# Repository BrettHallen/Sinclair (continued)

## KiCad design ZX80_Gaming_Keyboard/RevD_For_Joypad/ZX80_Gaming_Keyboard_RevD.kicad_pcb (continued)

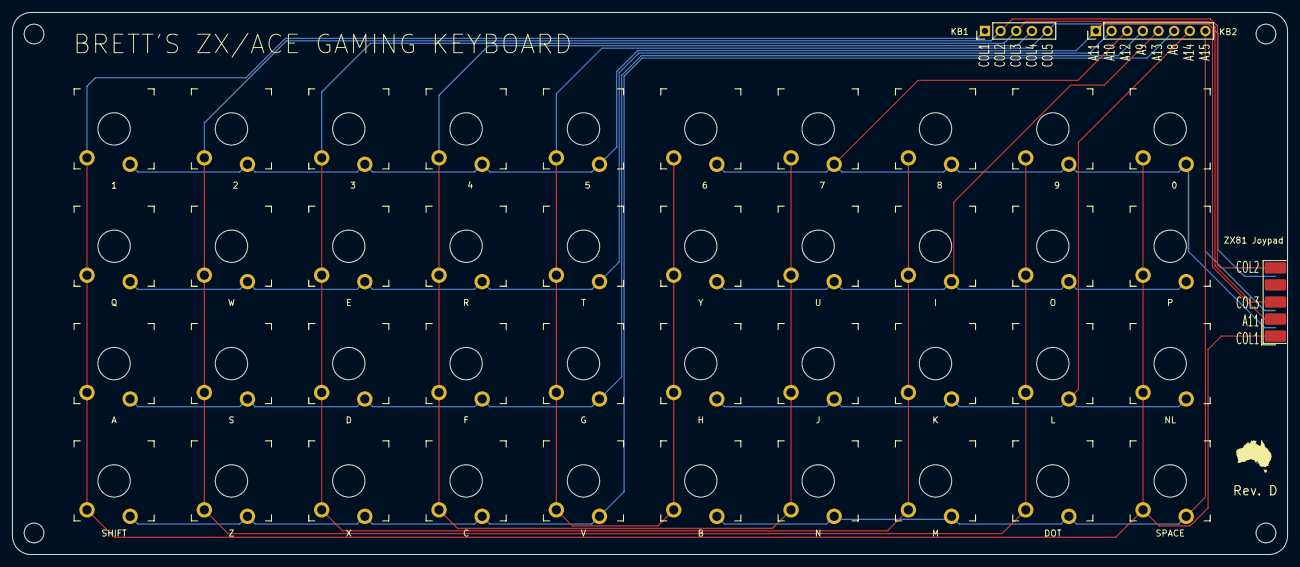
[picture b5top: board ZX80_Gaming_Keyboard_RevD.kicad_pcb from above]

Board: 2 copper layers, 207.0 x 88.0 mm, 47 parts (0 on the bottom side), 13 nets.

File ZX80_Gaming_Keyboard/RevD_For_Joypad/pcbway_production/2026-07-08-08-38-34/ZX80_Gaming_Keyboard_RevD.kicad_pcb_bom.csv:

Designator,Quantity,Value,Footprint,Package,MPN,DNP,Mount_Type,Description,KiLib_Generator
J1,1,KB1,PinHeader_1x05_P2.54mm_Vertical,,,,tht,"Generic connector, single row, 01x05, script generated (kicad-library-utils/schlib/autogen/connector/)",
J2,1,ZX81 Joypad,DSUB-9_Pins_EdgeMount_P2.77mm,,,,smt,"9-pin D-SUB connector, pins (male)",connector/D_sub
J3,1,KB2,PinHeader_1x08_P2.54mm_Vertical,,,,tht,"Generic connector, single row, 01x08, script generated (kicad-library-utils/schlib/autogen/connector/)",
SW1,1,1,SW_Gateron_LowProfile_THT,,,,tht,"Push button switch, normally open, two pins, 45° tilted",
SW10,1,E,SW_Gateron_LowProfile_THT,,,,tht,"Push button switch, normally open, two pins, 45° tilted",
SW11,1,D,SW_Gateron_LowProfile_THT,,,,tht,"Push button switch, normally open, two pins, 45° tilted",
SW12,1,X,SW_Gateron_LowProfile_THT,,,,tht,"Push button switch, normally open, two pins, 45° tilted",
SW13,1,4,SW_Gateron_LowProfile_THT,,,,tht,"Push button switch, normally open, two pins, 45° tilted",
SW14,1,R,SW_Gateron_LowProfile_THT,,,,tht,"Push button switch, normally open, two pins, 45° tilted",
SW15,1,F,SW_Gateron_LowProfile_THT,,,,tht,"Push button switch, normally open, two pins, 45° tilted",
SW16,1,C,SW_Gateron_LowProfile_THT,,,,tht,"Push button switch, normally open, two pins, 45° tilted",
SW17,1,5,SW_Gateron_LowProfile_THT,,,,tht,"Push button switch, normally open, two pins, 45° tilted",
SW18,1,T,SW_Gateron_LowProfile_THT,,,,tht,"Push button switch, normally open, two pins, 45° tilted",
SW19,1,G,SW_Gateron_LowProfile_THT,,,,tht,"Push button switch, normally open, two pins, 45° tilted",
SW2,1,Q,SW_Gateron_LowProfile_THT,,,,tht,"Push button switch, normally open, two pins, 45° tilted",
SW20,1,V,SW_Gateron_LowProfile_THT,,,,tht,"Push button switch, normally open, two pins, 45° tilted",
SW21,1,6,SW_Gateron_LowProfile_THT,,,,tht,"Push button switch, normally open, two pins, 45° tilted",
SW22,1,Y,SW_Gateron_LowProfile_THT,,,,tht,"Push button switch, normally open, two pins, 45° tilted",
SW23,1,H,SW_Gateron_LowProfile_THT,,,,tht,"Push button switch, normally open, two pins, 45° tilted",
SW24,1,B,SW_Gateron_LowProfile_THT,,,,tht,"Push button switch, normally open, two pins, 45° tilted",
SW25,1,7,SW_Gateron_LowProfile_THT,,,,tht,"Push button switch, normally open, two pins, 45° tilted",
SW26,1,U,SW_Gateron_LowProfile_THT,,,,tht,"Push button switch, normally open, two pins, 45° tilted",
SW27,1,J,SW_Gateron_LowProfile_THT,,,,tht,"Push button switch, normally open, two pins, 45° tilted",
SW28,1,N,SW_Gateron_LowProfile_THT,,,,tht,"Push button switch, normally open, two pins, 45° tilted",
SW29,1,8,SW_Gateron_LowProfile_THT,,,,tht,"Push button switch, normally open, two pins, 45° tilted",
SW3,1,A,SW_Gateron_LowProfile_THT,,,,tht,"Push button switch, normally open, two pins, 45° tilted",
SW30,1,I,SW_Gateron_LowProfile_THT,,,,tht,"Push button switch, normally open, two pins, 45° tilted",
SW31,1,K,SW_Gateron_LowProfile_THT,,,,tht,"Push button switch, normally open, two pins, 45° tilted",
SW32,1,M,SW_Gateron_LowProfile_THT,,,,tht,"Push button switch, normally open, two pins, 45° tilted",
SW33,1,9,SW_Gateron_LowProfile_THT,,,,tht,"Push button switch, normally open, two pins, 45° tilted",
SW34,1,O,SW_Gateron_LowProfile_THT,,,,tht,"Push button switch, normally open, two pins, 45° tilted",
SW35,1,L,SW_Gateron_LowProfile_THT,,,,tht,"Push button switch, normally open, two pins, 45° tilted",
SW36,1,DOT,SW_Gateron_LowProfile_THT,,,,tht,"Push button switch, normally open, two pins, 45° tilted",
SW37,1,0,SW_Gateron_LowProfile_THT,,,,tht,"Push button switch, normally open, two pins, 45° tilted",
SW38,1,P,SW_Gateron_LowProfile_THT,,,,tht,"Push button switch, normally open, two pins, 45° tilted",
SW39,1,NL,SW_Gateron_LowProfile_THT,,,,tht,"Push button switch, normally open, two pins, 45° tilted",
SW4,1,SHIFT,SW_Gateron_LowProfile_THT,,,,tht,"Push button switch, normally open, two pins, 45° tilted",
SW40,1,SPACE,SW_Gateron_LowProfile_THT,,,,tht,"Push button switch, normally open, two pins, 45° tilted",
SW5,1,2,SW_Gateron_LowProfile_THT,,,,tht,"Push button switch, normally open, two pins, 45° tilted",
SW6,1,W,SW_Gateron_LowProfile_THT,,,,tht,"Push button switch, normally open, two pins, 45° tilted",
SW7,1,S,SW_Gateron_LowProfile_THT,,,,tht,"Push button switch, normally open, two pins, 45° tilted",
SW8,1,Z,SW_Gateron_LowProfile_THT,,,,tht,"Push button switch, normally open, two pins, 45° tilted",
SW9,1,3,SW_Gateron_LowProfile_THT,,,,tht,"Push button switch, normally open, two pins, 45° tilted",

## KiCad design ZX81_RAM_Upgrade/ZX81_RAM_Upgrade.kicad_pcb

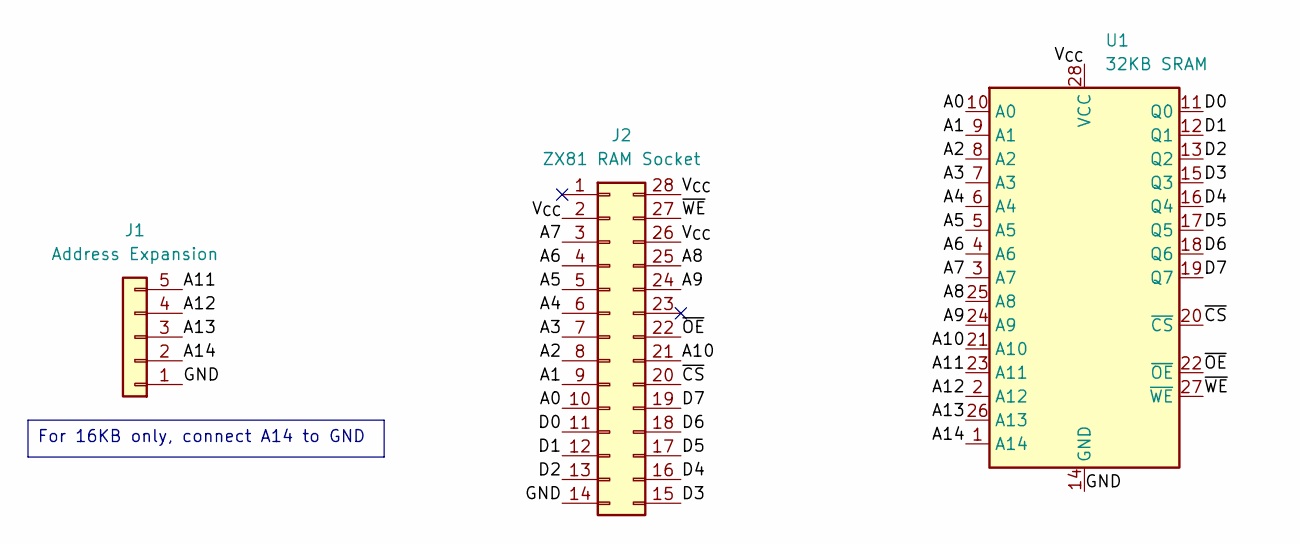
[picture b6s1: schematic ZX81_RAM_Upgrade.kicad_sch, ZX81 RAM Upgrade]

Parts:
J1: Address Expansion; PinHeader_1x05_P2.54mm_Vertical
J2: ZX81 RAM Socket; DIP-28_W15.24mm_Socket
U1: 32KB SRAM; DIP-28_W15.24mm

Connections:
/A0: J2.10, U1.10 (A0)
/A1: J2.9, U1.9 (A1)
/A2: J2.8, U1.8 (A2)
/A3: J2.7, U1.7 (A3)
/A4: J2.6, U1.6 (A4)
/A5: J2.5, U1.5 (A5)
/A6: J2.4, U1.4 (A6)
/A7: J2.3, U1.3 (A7)
/A8: J2.25, U1.25 (A8)
/A9: J2.24, U1.24 (A9)
/A10: J2.21, U1.21 (A10)
/A11: J1.5, U1.23 (A11)
/A12: J1.4, U1.2 (A12)
/A13: J1.3, U1.26 (A13)
/A14: J1.2, U1.1 (A14)
/D0: J2.11, U1.11 (Q0)
/D1: J2.12, U1.12 (Q1)
/D2: J2.13, U1.13 (Q2)
/D3: J2.15, U1.15 (Q3)
/D4: J2.16, U1.16 (Q4)
/D5: J2.17, U1.17 (Q5)
/D6: J2.18, U1.18 (Q6)
/D7: J2.19, U1.19 (Q7)
/GND: J1.1, J2.14, U1.14 (GND)
/V_{CC}: J2.2, J2.26, J2.28, U1.28 (VCC)
/~CS: J2.20, U1.20 (~CS)
/~OE: J2.22, U1.22 (~OE)
/~WE: J2.27, U1.27 (~WE)

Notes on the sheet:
For 16KB only, connect A14 to GND

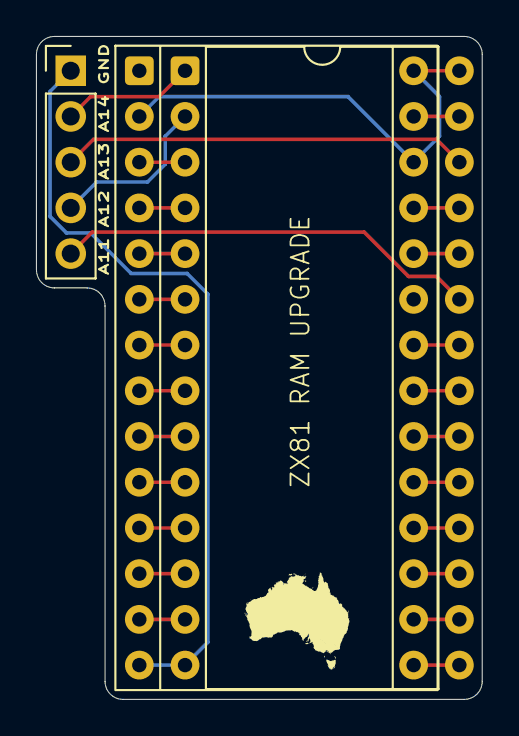
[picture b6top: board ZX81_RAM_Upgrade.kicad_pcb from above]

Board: 2 copper layers, 24.8 x 36.8 mm, 3 parts (0 on the bottom side), 28 nets.

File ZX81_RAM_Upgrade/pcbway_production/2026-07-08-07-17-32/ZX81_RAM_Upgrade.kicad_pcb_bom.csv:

Designator,Quantity,Value,Footprint,Package,MPN,DNP,Mount_Type,Description,KiLib_Generator
J1,1,Address Expansion,PinHeader_1x05_P2.54mm_Vertical,,,,tht,"Generic connector, single row, 01x05, script generated (kicad-library-utils/schlib/autogen/connector/)",connector/pin_header_socket
J2,1,ZX81 RAM Socket,DIP-28_W15.24mm_Socket,,,,tht,"Generic connector, double row, 02x14, counter clockwise pin numbering scheme (similar to DIP package numbering), script generated (kicad-library-utils/schlib/autogen/connector/)",package/DIP/legacy
U1,1,32KB SRAM,DIP-28_W15.24mm,,,,tht,"32Kx8 bit Low Power CMOS Static RAM, 55/70ns, DIP-28",package/DIP/legacy

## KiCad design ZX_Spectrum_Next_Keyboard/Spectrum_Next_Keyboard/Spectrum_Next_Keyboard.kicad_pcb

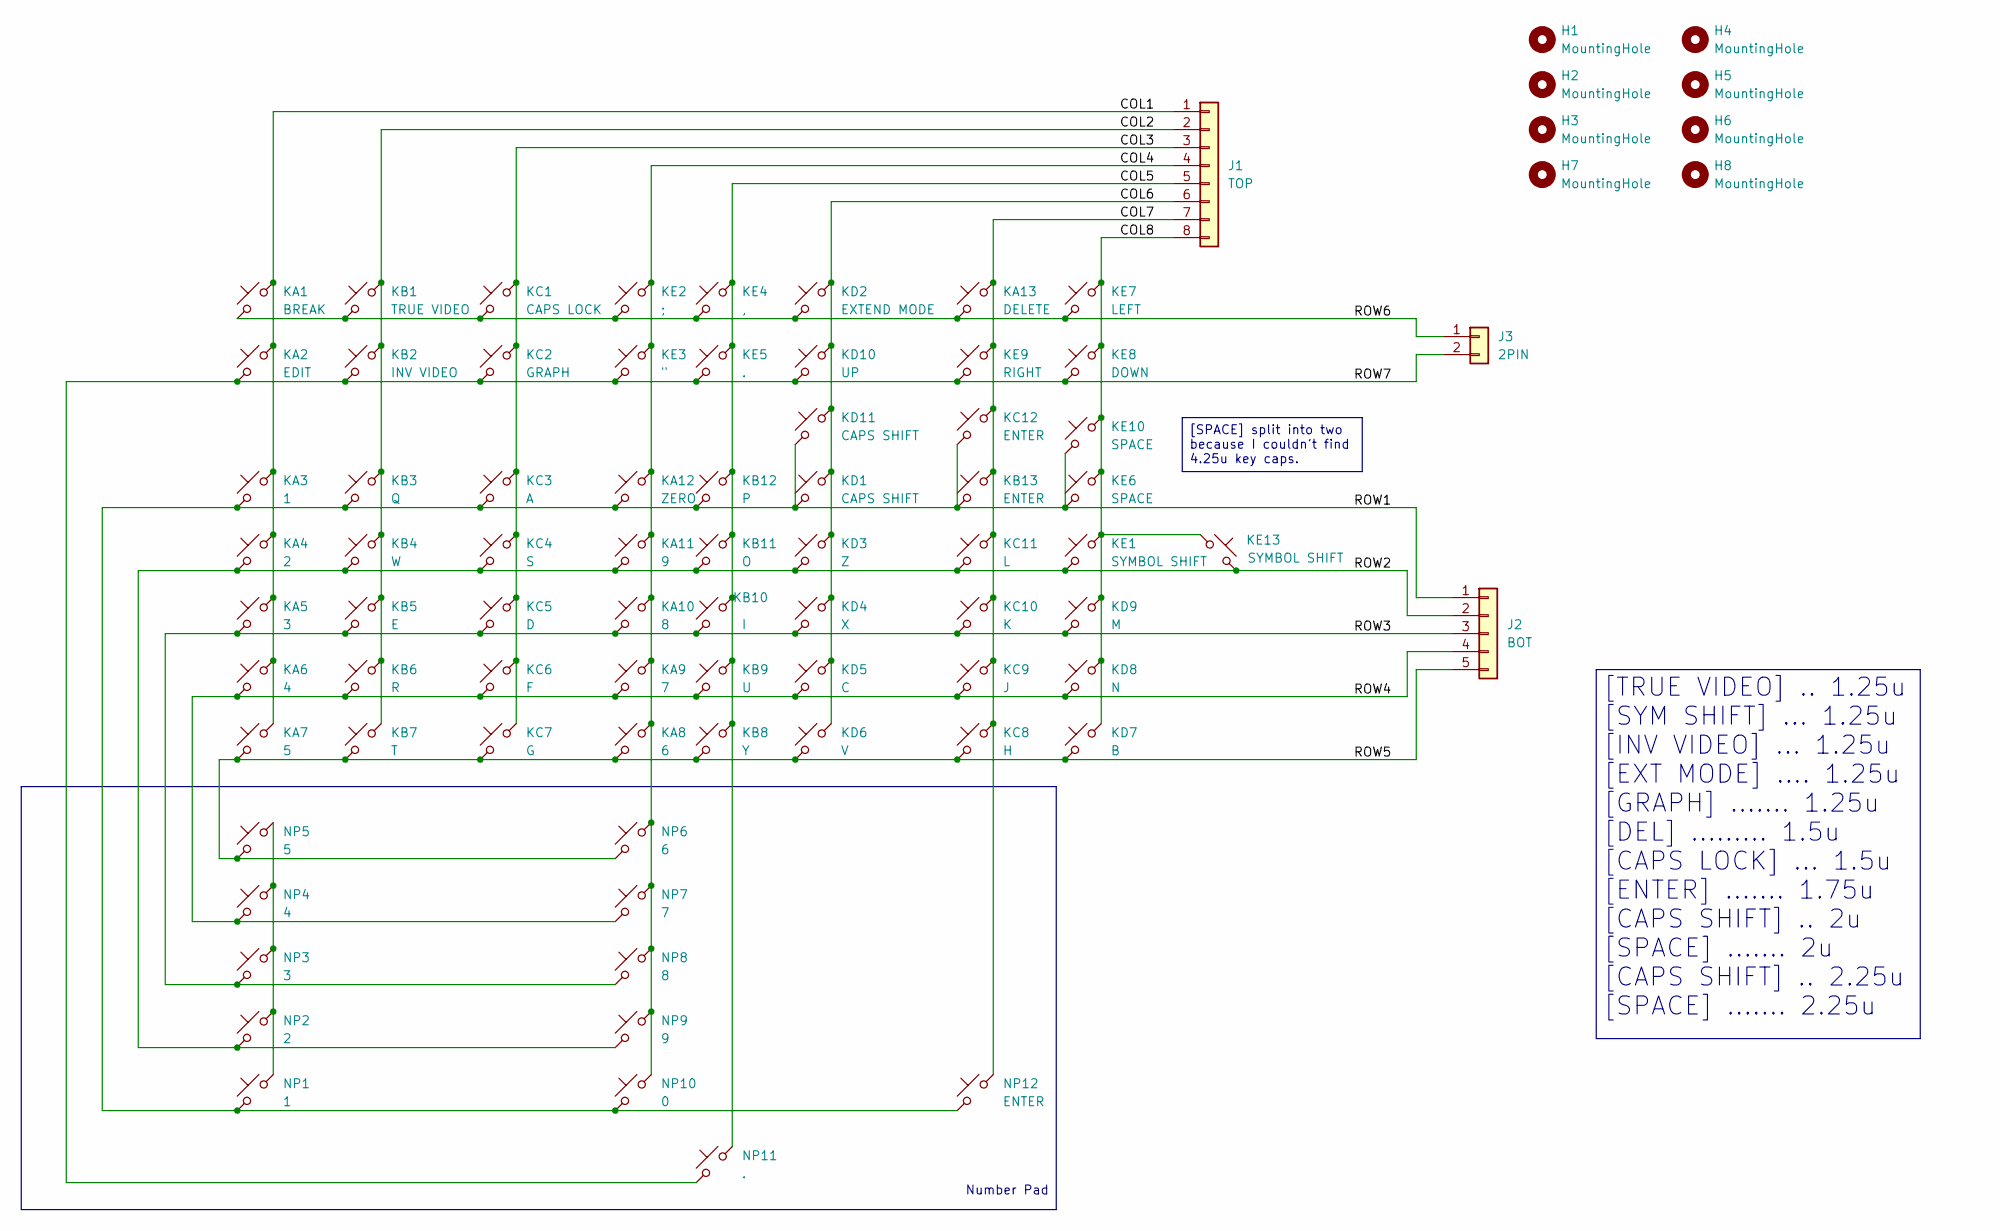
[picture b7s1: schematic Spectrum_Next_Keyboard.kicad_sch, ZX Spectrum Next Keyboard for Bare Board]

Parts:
H1, H2, H3, H4, H5, H6, H7, H8: MountingHole; MountingHole_3.2mm_M3
J1: TOP; PinHeader_1x08_P2.54mm_Vertical
J2: BOT; PinHeader_1x05_P2.54mm_Vertical
J3: 2PIN; PinHeader_1x02_P2.54mm_Vertical
KA1: BREAK; SW_Gateron_LowProfile_THT
KA2: EDIT; SW_Gateron_LowProfile_THT
KA3: 1; SW_Gateron_LowProfile_THT
KA4: 2; SW_Gateron_LowProfile_THT
KA5: 3; SW_Gateron_LowProfile_THT
KA6: 4; SW_Gateron_LowProfile_THT
KA7: 5; SW_Gateron_LowProfile_THT
KA8: 6; SW_Gateron_LowProfile_THT
KA9: 7; SW_Gateron_LowProfile_THT
KA10: 8; SW_Gateron_LowProfile_THT
KA11: 9; SW_Gateron_LowProfile_THT
KA12: ZERO; SW_Gateron_LowProfile_THT
KA13: DELETE; SW_Gateron_LowProfile_THT
KB1: TRUE VIDEO; SW_Gateron_LowProfile_THT
KB2: INV VIDEO; SW_Gateron_LowProfile_THT
KB3: Q; SW_Gateron_LowProfile_THT
KB4: W; SW_Gateron_LowProfile_THT
KB5: E; SW_Gateron_LowProfile_THT
KB6: R; SW_Gateron_LowProfile_THT
KB7: T; SW_Gateron_LowProfile_THT
KB8: Y; SW_Gateron_LowProfile_THT
KB9: U; SW_Gateron_LowProfile_THT
KB10: I; SW_Gateron_LowProfile_THT
KB11: O; SW_Gateron_LowProfile_THT
KB12: P; SW_Gateron_LowProfile_THT
KB13: ENTER; SW_Gateron_LowProfile_THT
KC1: CAPS LOCK; SW_Gateron_LowProfile_THT
KC2: GRAPH; SW_Gateron_LowProfile_THT
KC3: A; SW_Gateron_LowProfile_THT
KC4: S; SW_Gateron_LowProfile_THT
KC5: D; SW_Gateron_LowProfile_THT
KC6: F; SW_Gateron_LowProfile_THT
KC7: G; SW_Gateron_LowProfile_THT
KC8: H; SW_Gateron_LowProfile_THT
KC9: J; SW_Gateron_LowProfile_THT
KC10: K; SW_Gateron_LowProfile_THT
KC11: L; SW_Gateron_LowProfile_THT
KC12: ENTER; SW_Gateron_LowProfile_THT
KD1, KD11: CAPS SHIFT; SW_Gateron_LowProfile_THT
KD2: EXTEND MODE; SW_Gateron_LowProfile_THT
KD3: Z; SW_Gateron_LowProfile_THT
KD4: X; SW_Gateron_LowProfile_THT
KD5: C; SW_Gateron_LowProfile_THT
KD6: V; SW_Gateron_LowProfile_THT
KD7: B; SW_Gateron_LowProfile_THT
KD8: N; SW_Gateron_LowProfile_THT
KD9: M; SW_Gateron_LowProfile_THT
KD10: UP; SW_Gateron_LowProfile_THT
KE1, KE13: SYMBOL SHIFT; SW_Gateron_LowProfile_THT
KE2: ;; SW_Gateron_LowProfile_THT
KE3: "; SW_Gateron_LowProfile_THT
KE4: ,; SW_Gateron_LowProfile_THT
KE5: .; SW_Gateron_LowProfile_THT
KE6, KE10: SPACE; SW_Gateron_LowProfile_THT
KE7: LEFT; SW_Gateron_LowProfile_THT
KE8: DOWN; SW_Gateron_LowProfile_THT
KE9: RIGHT; SW_Gateron_LowProfile_THT
NP1: 1; SW_Gateron_LowProfile_THT
NP2: 2; SW_Gateron_LowProfile_THT
NP3: 3; SW_Gateron_LowProfile_THT
NP4: 4; SW_Gateron_LowProfile_THT
NP5: 5; SW_Gateron_LowProfile_THT
NP6: 6; SW_Gateron_LowProfile_THT
NP7: 7; SW_Gateron_LowProfile_THT
NP8: 8; SW_Gateron_LowProfile_THT
NP9: 9; SW_Gateron_LowProfile_THT
NP10: 0; SW_Gateron_LowProfile_THT
NP11: .; SW_Gateron_LowProfile_THT
NP12: ENTER; SW_Gateron_LowProfile_THT

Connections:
/COL1: J1.1, KA1.2, KA2.2, KA3.2, KA4.2, KA5.2, KA6.2, KA7.2
/COL2: J1.2, KB1.2, KB2.2, KB3.2, KB4.2, KB5.2, KB6.2, KB7.2
/COL3: J1.3, KC1.2, KC2.2, KC3.2, KC4.2, KC5.2, KC6.2, KC7.2
/COL4: J1.4, KA8.2, KA9.2, KA10.2, KA11.2, KA12.2, KE2.2, KE3.2, NP6.2, NP7.2, NP8.2, NP9.2, NP10.2
/COL5: J1.5, KB8.2, KB9.2, KB10.2, KB11.2, KB12.2, KE4.2, KE5.2, NP11.2
/COL6: J1.6, KD1.2, KD2.2, KD3.2, KD4.2, KD5.2, KD6.2, KD10.2, KD11.2
/COL7: J1.7, KA13.2, KB13.2, KC8.2, KC9.2, KC10.2, KC11.2, KC12.2, KE9.2, NP12.2
/COL8: J1.8, KD7.2, KD8.2, KD9.2, KE1.2, KE6.2, KE7.2, KE8.2, KE10.2, KE13.2
/ROW1: J2.1, KA3.1, KA12.1, KB3.1, KB12.1, KB13.1, KC3.1, KC12.1, KD1.1, KD11.1, KE6.1, KE10.1, NP1.1, NP10.1, NP12.1
/ROW2: J2.2, KA4.1, KA11.1, KB4.1, KB11.1, KC4.1, KC11.1, KD3.1, KE1.1, KE13.1, NP2.1, NP9.1
/ROW3: J2.3, KA5.1, KA10.1, KB5.1, KB10.1, KC5.1, KC10.1, KD4.1, KD9.1, NP3.1, NP8.1
/ROW4: J2.4, KA6.1, KA9.1, KB6.1, KB9.1, KC6.1, KC9.1, KD5.1, KD8.1, NP4.1, NP7.1
/ROW5: J2.5, KA7.1, KA8.1, KB7.1, KB8.1, KC7.1, KC8.1, KD6.1, KD7.1, NP5.1, NP6.1
/ROW6: J3.1, KA1.1, KA13.1, KB1.1, KC1.1, KD2.1, KE2.1, KE4.1, KE7.1
/ROW7: J3.2, KA2.1, KB2.1, KC2.1, KD10.1, KE3.1, KE5.1, KE8.1, KE9.1, NP11.1
unnamed: NP1.2, NP2.2, NP3.2, NP4.2, NP5.2

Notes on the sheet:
Number Pad
[TRUE VIDEO] .. 1.25u [SYM SHIFT] ... 1.25u [INV VIDEO] ... 1.25u [EXT MODE] .... 1.25u [GRAPH] ....... 1.25u [DEL] ......... 1.5u [CAPS LOCK] ... 1.5u [ENTER] ....... 1.75u [CAPS SHIFT] .. 2u [SPACE] ....... 2u [CAPS SHIFT] .. 2.25u [SPACE] ....... 2.25u
[SPACE] split into two because I couldn't find 4.25u key caps.

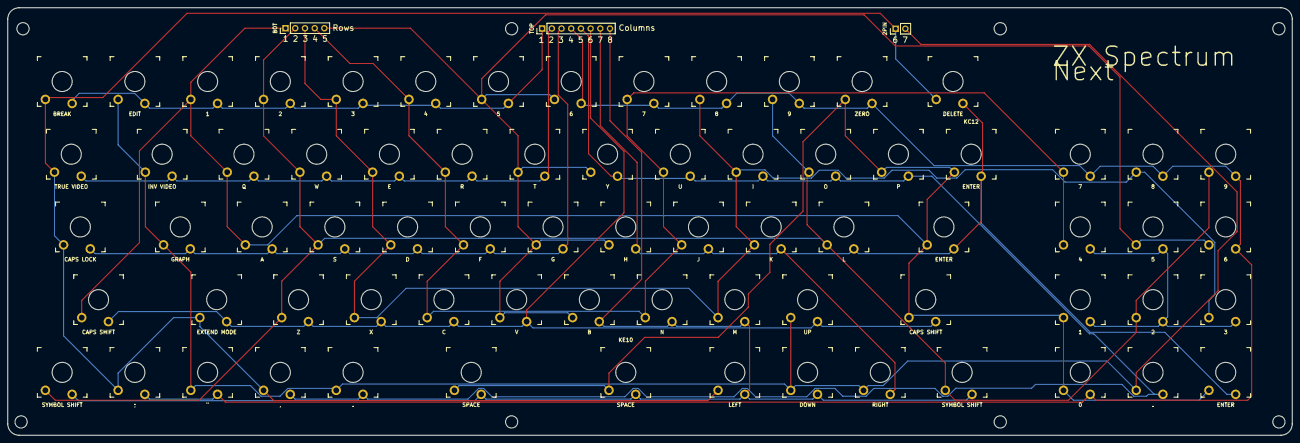
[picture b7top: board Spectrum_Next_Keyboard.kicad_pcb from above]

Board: 2 copper layers, 336.5 x 112.0 mm, 83 parts (0 on the bottom side), 16 nets.

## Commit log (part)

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2025-12-05 Corrected ENTER key location (duh)
2025-12-31 Initial design completed
2025-12-31 Rev. C
    Removed dedicated DEL key - still need to figure it out
2026-01-05 Added NumPad to keyboard
2026-01-06 Rerouted so no vias required
2026-06-01 Initial commit
    Simple joypad (replicating number/cursor keys) for my simple keyboard
2026-06-01 Modified layout with joypad connector
    Removed the cursor cluster and added pin header to my ZX80 Joypad
